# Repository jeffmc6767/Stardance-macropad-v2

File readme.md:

# Stardance Hackpad

My hackpad is a 3x3 keyboard with 2 rotary encoders controlled by a XIAO RP2040

---

## Media & Previews

### Overall Hackpad Preview

### Schematic Design

### PCB Layout & Routing

### Case Assembly & Fitment
The one on the left is the top, middle is the bottom and the one on the right is the middle. 

---

## Bill of Materials (BOM)
I also have a bom.csv 

- 1x XIAO RP2040
- 9x Cherry MX switches
- 9x DSA Keycaps
- 9x 1N4148 DO-35 Diodes.
- 10x WS2812B LEDs
- 2x EC11 Rotary Encoder
- 1x case(I have a 3d printer so I dont actually need funding for this)
- 4x M3x5mx4mm heatset inserts
- 4x M3x16mm screws

---

## Folder Navigation

* `/xiaopad` — Core QMK firmware files (`info.json`, `config.h`, `keymap.c`, `rules.mk`).
* `/kicad` — Main electronic design schemas and layout assets.
* `/Plotting for PCB` — Complete manufacturing Gerber production packages (zipped).

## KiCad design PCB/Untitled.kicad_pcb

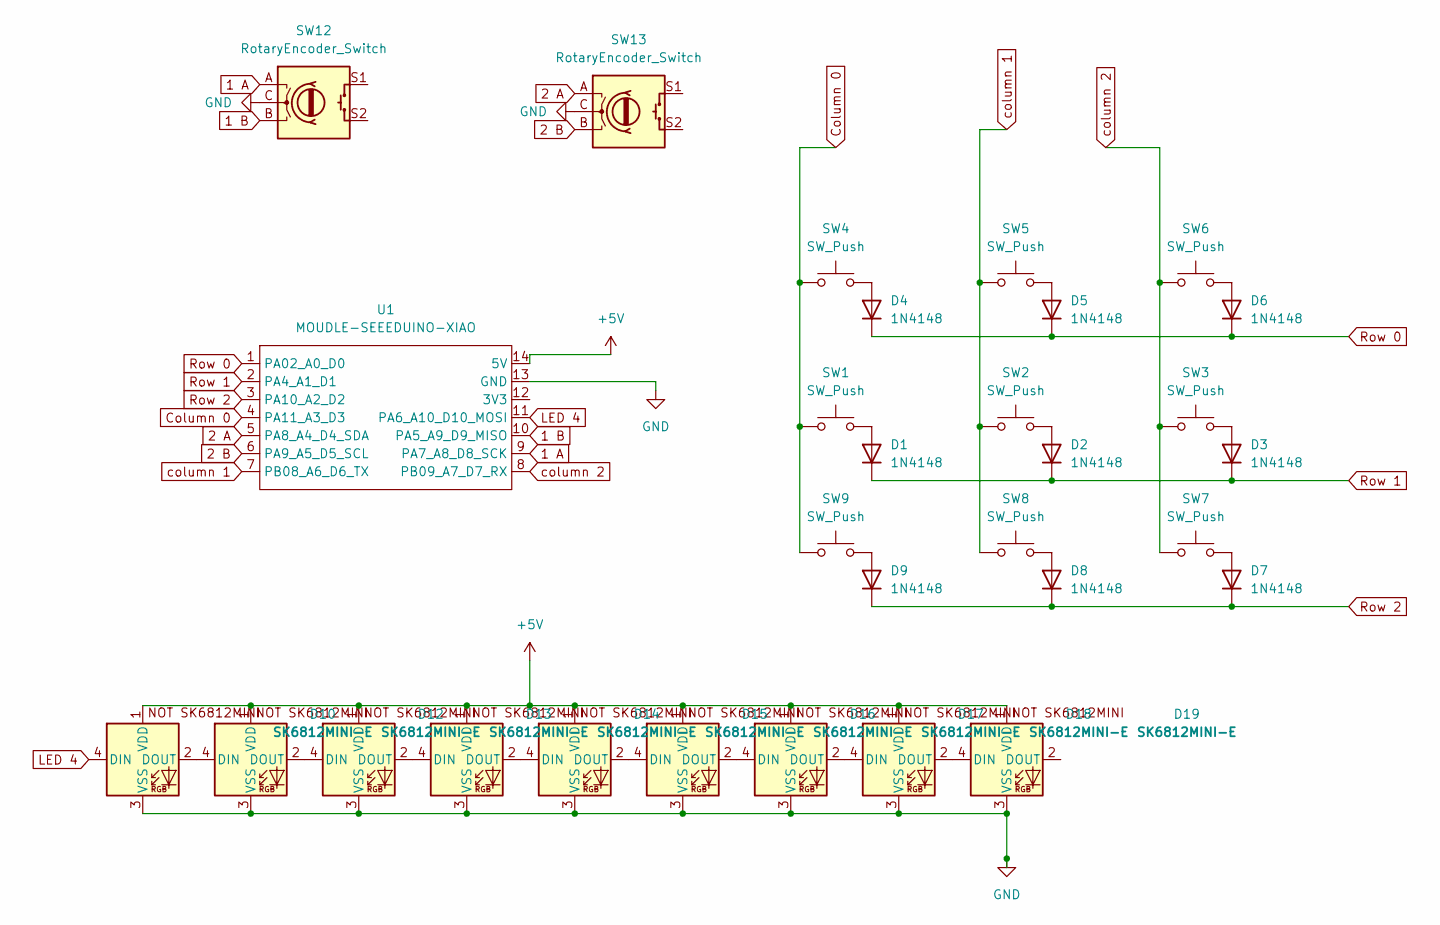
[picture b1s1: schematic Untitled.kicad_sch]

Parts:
D1, D2, D3, D4, D5, D6, D7, D8, D9: 1N4148; D_DO-35_SOD27_P7.62mm_Horizontal
D10, D12, D13, D14, D15, D16, D17, D18, D19: SK6812MINI-E; SK6812MINI-E_fixed
SW1, SW2, SW3, SW4, SW5, SW6, SW7, SW8, SW9: SW_Push; SW_Cherry_MX_1.00u_PCB
SW12: RotaryEncoder_Switch; RotaryEncoder_Alps_EC11E_Vertical_H20mm
SW13: RotaryEncoder_Switch; RotaryEncoder_Alps_EC11E-Switch_Vertical_H20mm
U1: MOUDLE-SEEEDUINO-XIAO; XIAO-Generic-Hybrid-14P-2.54-21X17.8MM

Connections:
1 A: SW12.A, U1.9 (PA7_A8_D8_SCK)
1 B: SW12.B, U1.10 (PA5_A9_D9_MISO)
2 A: SW13.A, U1.5 (PA8_A4_D4_SDA)
2 B: SW13.B, U1.6 (PA9_A5_D5_SCL)
+5V: D10.1 (VDD), D12.1 (VDD), D13.1 (VDD), D14.1 (VDD), D15.1 (VDD), D16.1 (VDD), D17.1 (VDD), D18.1 (VDD), D19.1 (VDD), U1.14 (5V)
Column 0: SW1.1, SW4.1, SW9.1, U1.4 (PA11_A3_D3)
GND: D10.3 (VSS), D12.3 (VSS), D13.3 (VSS), D14.3 (VSS), D15.3 (VSS), D16.3 (VSS), D17.3 (VSS), D18.3 (VSS), D19.3 (VSS), SW12.C, SW13.C, U1.13 (GND)
LED 4: D10.4 (DIN), U1.11 (PA6_A10_D10_MOSI)
unnamed: D1.2 (A), SW1.2
unnamed: D2.2 (A), SW2.2
unnamed: D3.2 (A), SW3.2
unnamed: D4.2 (A), SW4.2
unnamed: D5.2 (A), SW5.2
unnamed: D6.2 (A), SW6.2
unnamed: D7.2 (A), SW7.2
unnamed: D8.2 (A), SW8.2
unnamed: D9.2 (A), SW9.2
unnamed: D10.2 (DOUT), D12.4 (DIN)
unnamed: D12.2 (DOUT), D13.4 (DIN)
unnamed: D13.2 (DOUT), D14.4 (DIN)
unnamed: D14.2 (DOUT), D15.4 (DIN)
unnamed: D15.2 (DOUT), D16.4 (DIN)
unnamed: D16.2 (DOUT), D17.4 (DIN)
unnamed: D17.2 (DOUT), D18.4 (DIN)
unnamed: D18.2 (DOUT), D19.4 (DIN)
Row 0: D4.1 (K), D5.1 (K), D6.1 (K), U1.1 (PA02_A0_D0)
Row 1: D1.1 (K), D2.1 (K), D3.1 (K), U1.2 (PA4_A1_D1)
Row 2: D7.1 (K), D8.1 (K), D9.1 (K), U1.3 (PA10_A2_D2)
column 1: SW2.1, SW5.1, SW8.1, U1.7 (PB08_A6_D6_TX)
column 2: SW3.1, SW6.1, SW7.1, U1.8 (PB09_A7_D7_RX)

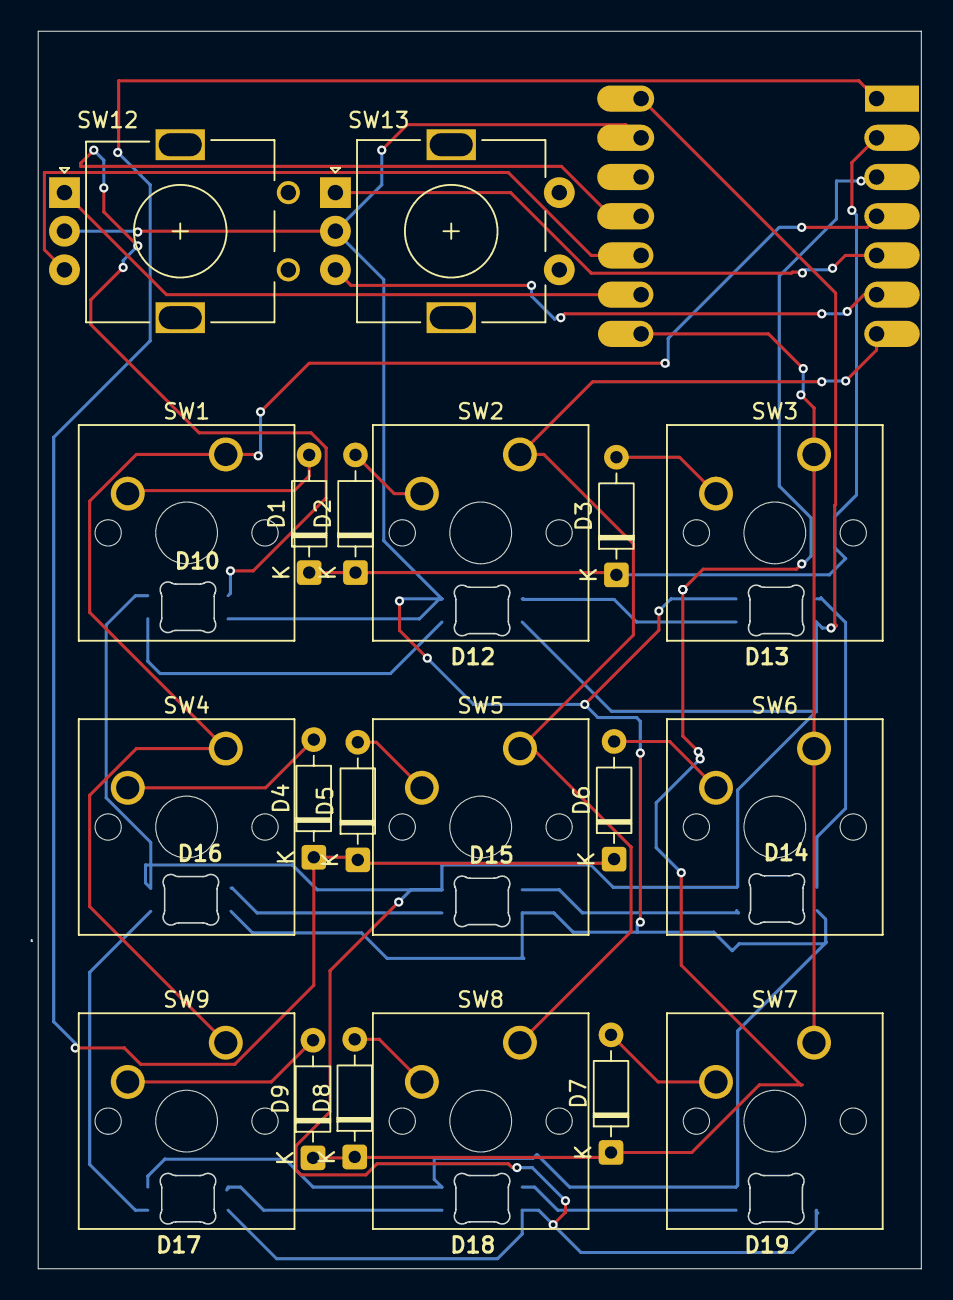
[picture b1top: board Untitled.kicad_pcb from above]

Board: 2 copper layers, 57.2 x 80.2 mm, 30 parts (1 on the bottom side), 30 nets.

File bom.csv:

"Id";"Designator";"Footprint";"Quantity";"Designation";"Supplier and ref";
1;"D1, D2, D3, D4, D5, D6, D7, D8, D9";"D_DO-35_SOD27_P7.62mm_Horizontal";9;"1N4148";;;
2;"D10, D12, D13, D14, D15, D16, D17, D18, D19";"SK6812MINI-E_fixed";9;"SK6812MINI-E";;;
3;"SW1, SW2, SW3, SW4, SW5, SW6, SW7, SW8, SW9";"SW_Cherry_MX_1.00u_PCB";9;"SW_Push";;;
4;"SW12";"RotaryEncoder_Alps_EC11E_Vertical_H20mm";1;"RotaryEncoder_Switch";;;
5;"SW13";"RotaryEncoder_Alps_EC11E-Switch_Vertical_H20mm";1;"RotaryEncoder_Switch";;;
6;"U1";"XIAO-Generic-Hybrid-14P-2.54-21X17.8MM";1;"MOUDLE-SEEEDUINO-XIAO";;;
